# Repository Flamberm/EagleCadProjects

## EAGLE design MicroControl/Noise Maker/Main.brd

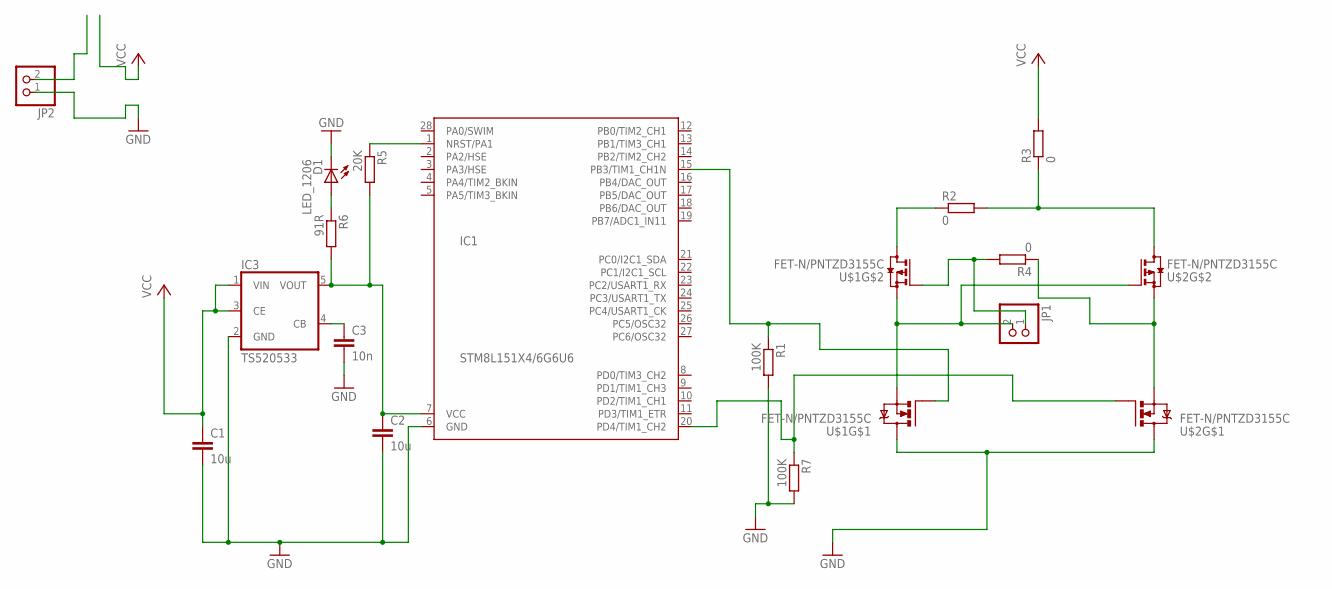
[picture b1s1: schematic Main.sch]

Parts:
C1, C2: 10u; C0805
C3: 10n; C0805
D1: LED_1206; LED1206
IC1: STM8L151X4/6G6U6; QFN28
IC3: TS520533; SOT25
JP1, JP2: PINHD-1X2; 1X02
R1, R7: 100K; R0805
R2, R3, R4: 0; R0805
R5: 20K; R0805
R6: 91R; R0805
U$1, U$2: FET-N/PNTZD3155C; SOT-563

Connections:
GND: C1.2, C2.2, C3.2, D1.C, IC1.6 (GND), IC3.2 (GND), JP2.1, R1.2, R7.2, U$1.6 (D), U$2.6 (D)
unnamed: D1.A, R6.1
unnamed: C3.1, IC3.4 (CB)
unnamed: IC1.1 (NRST/PA1), R5.1
unnamed: C2.1, IC1.7 (VCC), IC3.5 (VOUT), R5.2, R6.2
unnamed: R4.1, U$2.1 (S), U$2.4 (S)
unnamed: JP1.2, U$1.1 (S), U$1.4 (S), U$2.5 (G)
unnamed: IC1.20 (PD4/TIM1_CH2), R7.1, U$2.2 (G)
unnamed: R2.1, U$1.3 (D)
unnamed: R2.2, R3.1, U$2.3 (D)
unnamed: JP1.1, R4.2, U$1.5 (G)
unnamed: IC1.15 (PB3/TIM1_CH1N), R1.1, U$1.2 (G)
VCC: C1.1, IC3.1 (VIN), IC3.3 (CE), R3.2

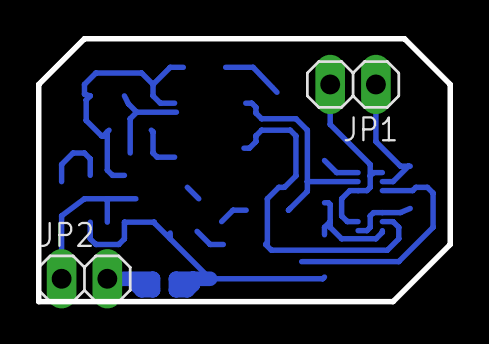
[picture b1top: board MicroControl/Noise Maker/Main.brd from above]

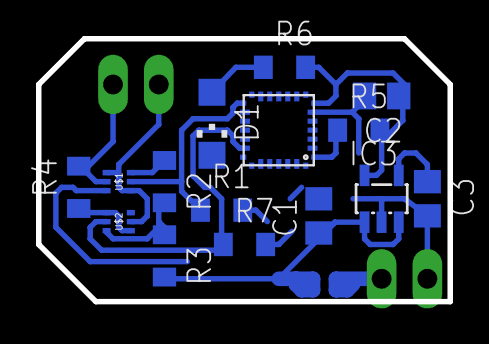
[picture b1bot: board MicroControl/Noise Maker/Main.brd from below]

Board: 2 copper layers, 22.9 x 14.6 mm, 17 parts (15 on the bottom side), 13 nets.

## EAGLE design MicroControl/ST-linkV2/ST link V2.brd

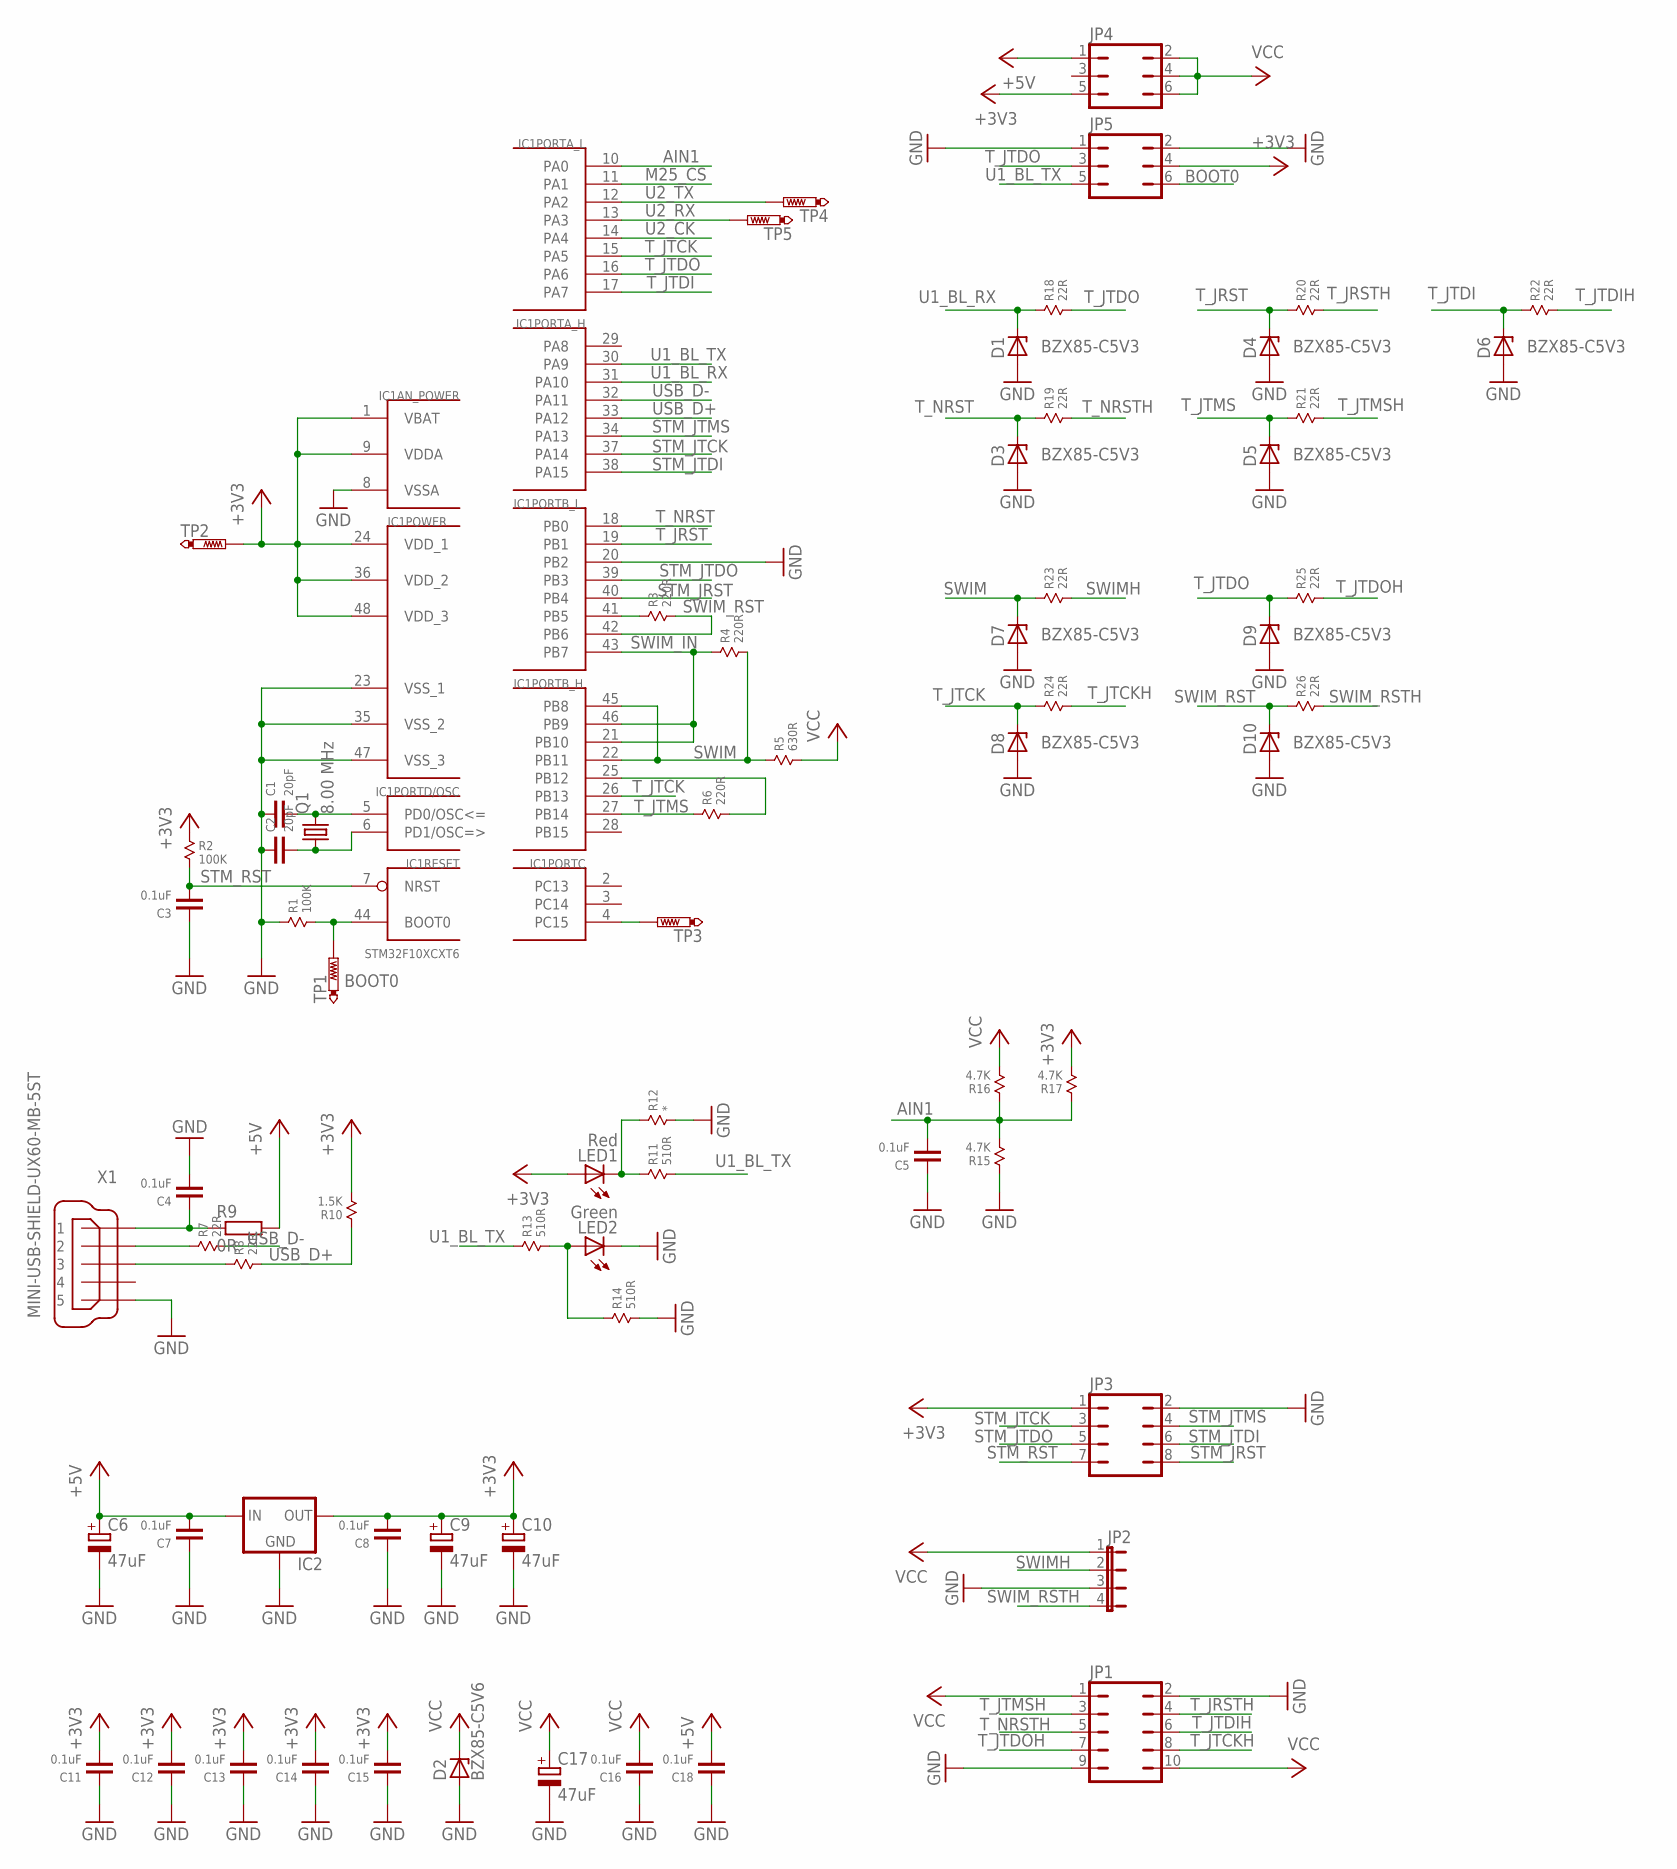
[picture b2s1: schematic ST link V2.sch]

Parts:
C1, C2: 20pF; X893_0805
C3, C4, C5, C7, C8, C11, C12, C13, C14, C15, C16, C18: 0.1uF; X893_0805
C6, C9, C10, C17: 47uF; SMC_B
D1, D3, D4, D5, D6, D7, D8, D9, D10: BZX85-C5V3; SOD80C
D2: BZX85-C5V6; SOD80C
IC1: STM32F10XCXT6; TQFP48
IC2: LM1117; SOT223
JP1: JP5Q
JP2: JP4E; JP4
JP3: JP4Q
JP4, JP5: JP3Q
LED1: Red; SML0805
LED2: Green; SML0805
Q1: 8.00 MHz; HC49U70
R1, R2: 100K; X893_0805
R3, R4, R6: 220R; X893_0805
R5: 630R; X893_0805
R7, R8, R18, R19, R20, R21, R22, R23, R24, R25, R26: 22R; X893_0805
R9: 0R; R1206
R10: 1.5K; X893_0805
R11, R13, R14: 510R; X893_0805
R12: *; X893_0805
R15, R16, R17: 4.7K; X893_0805
TP1, TP2, TP3, TP4, TP5: PTR1TP19R; TP19R
X1: MINI-USB-SHIELD-UX60-MB-5ST; UX60-MB-5ST

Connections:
+3V3: C8.1, C9.+, C10.+, C11.1, C12.1, C13.1, C14.1, C15.1, IC1.1 (VBAT), IC1.9 (VDDA), IC1.24 (VDD_1), IC1.36 (VDD_2), IC1.48 (VDD_3), IC2.2 (OUT), JP3.1, JP4.5, JP5.4, LED1.A, R2.1, R10.2, R17.2, TP2.TP
+5V: C6.+, C7.1, C18.1, IC2.3 (IN), JP4.1, R9.2
AIN1: C5.1, IC1.10 (PA0), R15.2, R16.1, R17.1
BOOT0: IC1.44 (BOOT0), JP5.6, R1.2, TP1.TP
GND: C1.2, C2.2, C3.2, C4.1, C5.2, C6.-, C7.2, C8.2, C9.-, C10.-, C11.2, C12.2, C13.2, C14.2, C15.2, C16.2, C17.-, C18.2, D1.A, D2.A, D3.A, D4.A, D5.A, D6.A, D7.A, D8.A, D9.A, D10.A, IC1.8 (VSSA), IC1.20 (PB2), IC1.23 (VSS_1), IC1.35 (VSS_2), IC1.47 (VSS_3), IC2.1 (GND), JP1.2, JP1.9, JP2.3, JP3.2, JP5.1, JP5.2, LED2.C, R1.1, R12.2, R14.2, R15.1, X1.5
M25_CS: IC1.11 (PA1)
unnamed: C1.1, IC1.5 (PD0/OSC<=), Q1.2
unnamed: C2.1, IC1.6 (PD1/OSC=>), Q1.1
unnamed: IC1.4 (PC15), TP3.TP
unnamed: C4.2, R9.1, X1.1
unnamed: IC1.25 (PB12), R6.2
unnamed: R7.1, X1.2
unnamed: R8.1, X1.3
unnamed: LED1.C, R11.1, R12.1
unnamed: IC1.41 (PB5), R3.1
unnamed: LED2.A, R13.2, R14.1
STM_JRST: IC1.40 (PB4), JP3.8
STM_JTCK: IC1.37 (PA14), JP3.3
STM_JTDI: IC1.38 (PA15), JP3.6
STM_JTDO: IC1.39 (PB3), JP3.5
STM_JTMS: IC1.34 (PA13), JP3.4
STM_RST: C3.1, IC1.7 (NRST), JP3.7, R2.2
SWIM: D7.C, IC1.22 (PB11), IC1.45 (PB8), R4.2, R5.1, R23.1
SWIMH: JP2.2, R23.2
SWIM_IN: IC1.21 (PB10), IC1.43 (PB7), IC1.46 (PB9), R4.1
SWIM_RST: D10.C, IC1.42 (PB6), R3.2, R26.1
SWIM_RSTH: JP2.4, R26.2
T_JRST: D4.C, IC1.19 (PB1), R20.1
T_JRSTH: JP1.4, R20.2
T_JTCK: D8.C, IC1.15 (PA5), IC1.26 (PB13), R24.1
T_JTCKH: JP1.8, R24.2
T_JTDI: D6.C, IC1.17 (PA7), R22.1
T_JTDIH: JP1.6, R22.2
T_JTDO: D9.C, IC1.16 (PA6), JP5.3, R18.2, R25.1
T_JTDOH: JP1.7, R25.2
T_JTMS: D5.C, IC1.27 (PB14), R6.1, R21.1
T_JTMSH: JP1.3, R21.2
T_NRST: D3.C, IC1.18 (PB0), R19.1
T_NRSTH: JP1.5, R19.2
U1_BL_RX: D1.C, IC1.31 (PA10), R18.1
U1_BL_TX: IC1.30 (PA9), JP5.5, R11.2, R13.1
U2_CK: IC1.14 (PA4)
U2_RX: IC1.13 (PA3), TP5.TP
U2_TX: IC1.12 (PA2), TP4.TP
USB_D+: IC1.33 (PA12), R8.2, R10.1
USB_D-: IC1.32 (PA11), R7.2
VCC: C16.1, C17.+, D2.C, JP1.1, JP1.10, JP2.1, JP4.2, JP4.4, JP4.6, R5.2, R16.2

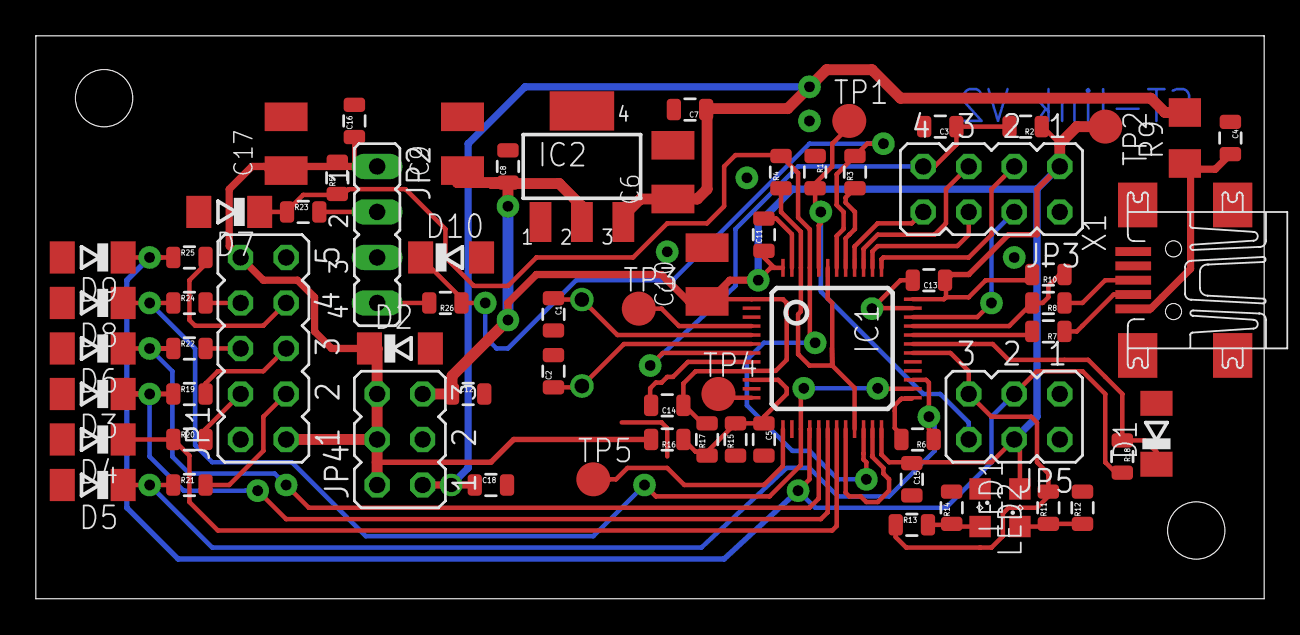
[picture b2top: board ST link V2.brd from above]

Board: 2 copper layers, 68.6 x 31.4 mm, 70 parts (1 on the bottom side), 45 nets.

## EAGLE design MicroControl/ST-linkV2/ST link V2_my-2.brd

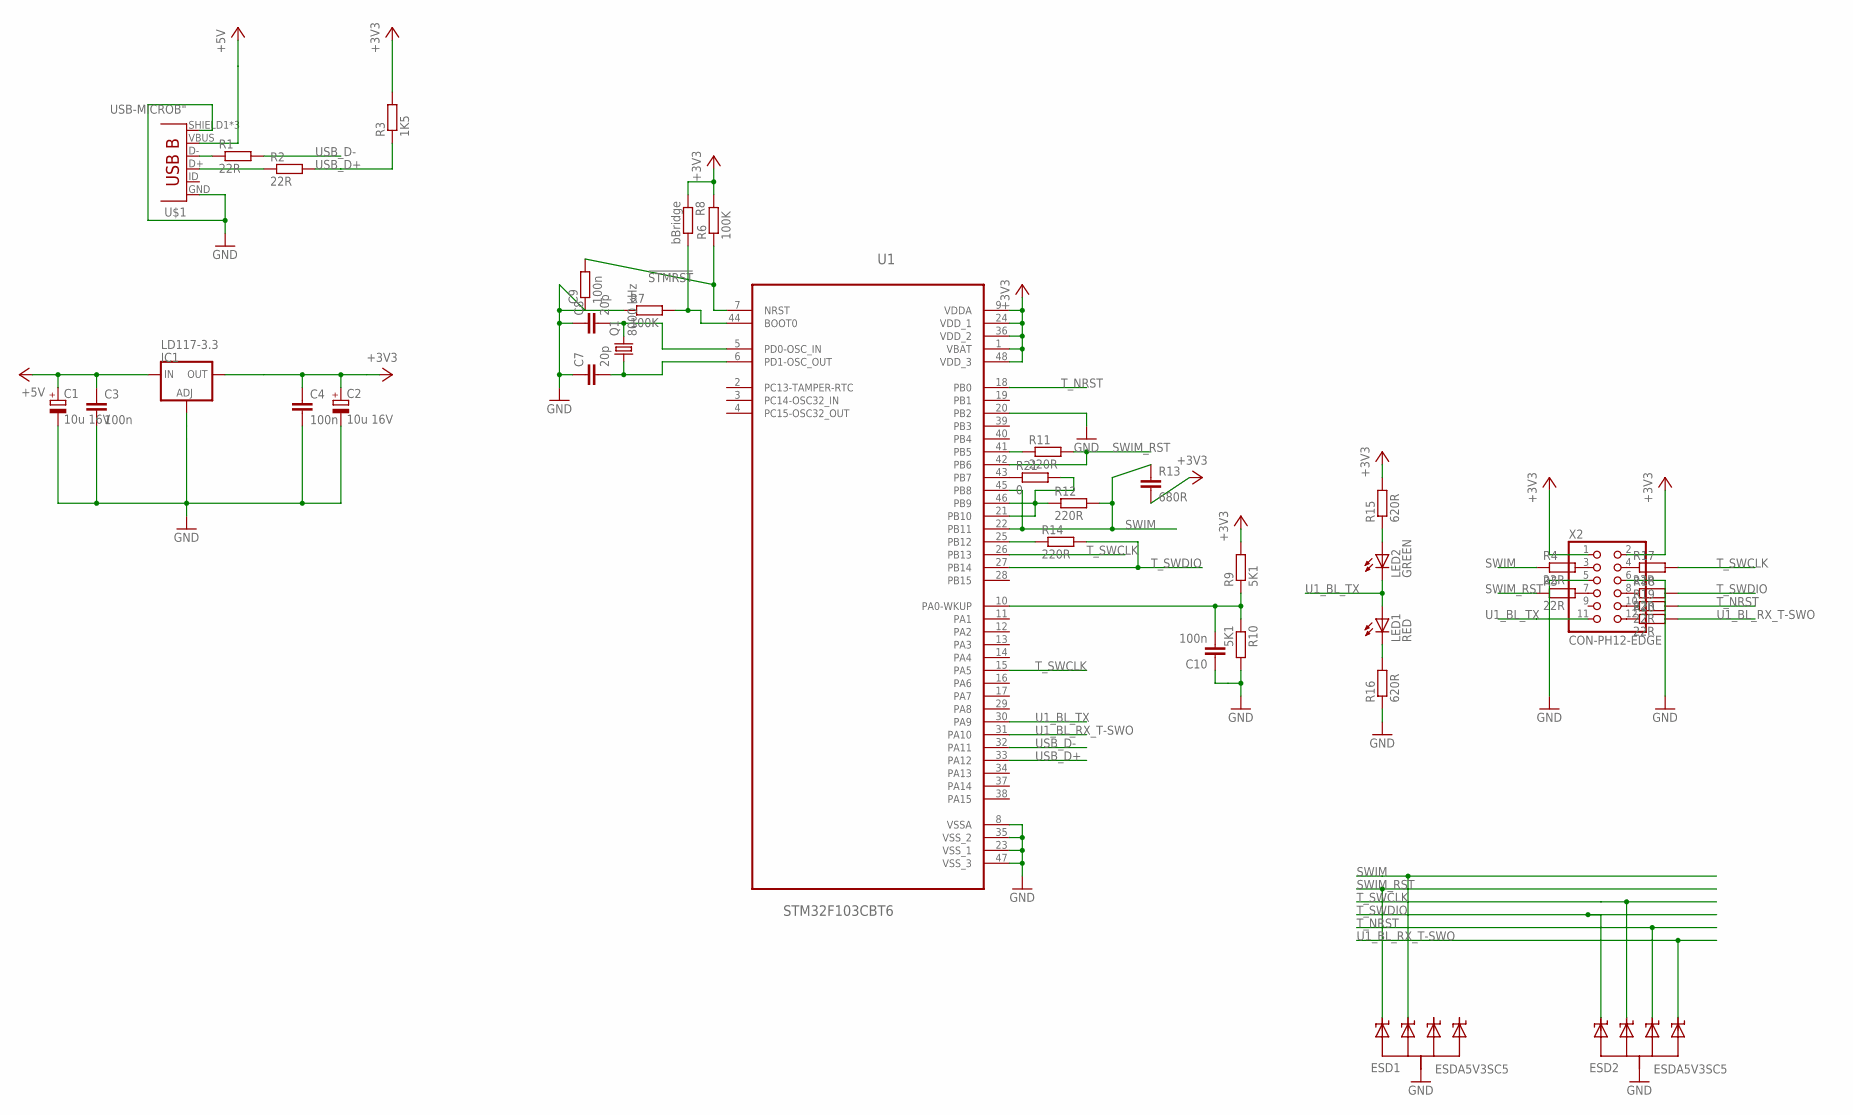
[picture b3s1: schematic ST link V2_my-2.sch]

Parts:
C1, C2: 10u 16V; SMC_A
C3, C4, C10: 100n; C0805
C7, C8: 20p; C0805
C9: 100n; R0805
ESD1, ESD2: ESDA5V3SC5; SOT23-5L
IC1: LD117-3.3; SOT223
LED1: RED; CHIPLED_1206
LED2: GREEN; CHIPLED_1206
Q1: 8000 kHz; HC49UP
R1, R2, R4, R5, R17, R18, R19, R20: 22R; R0805
R3: 1K5; R0805
R6, R7: 100K; R0805
R8: bBridge; R0805
R9, R10: 5K1; R0603
R11, R12, R14: 220R; R0805
R13: 680R; C0805
R15, R16: 620R; R0805
R21: 0; R0805
U1: STM32F103CBT6; QFP50P900X900X160-48N
U$1: USB-MICROB"; USB-B-MICRO-SMD_V03
X2: CON-PH12-EDGE; ML12_EDGE_SMD

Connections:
!STMRST: C9.2, R6.1, U1.7 (NRST)
+3V3: C2.+, C4.1, IC1.4 (OUT), R3.2, R6.2, R8.1, R9.2, R13.2, R15.2, U1.1 (VBAT), U1.9 (VDDA), U1.24 (VDD_1), U1.36 (VDD_2), U1.48 (VDD_3), X2.1, X2.2
+5V: C1.+, C3.1, IC1.3 (IN), U$1.VBUS
BOOT0: R7.2, R8.2, U1.44 (BOOT0)
GND: C1.-, C2.-, C3.2, C4.2, C7.1, C8.1, C9.1, C10.1, ESD1.2 (A), ESD2.2 (A), IC1.1 (ADJ), R7.1, R10.2, R16.1, U1.8 (VSSA), U1.20 (PB2), U1.23 (VSS_1), U1.35 (VSS_2), U1.47 (VSS_3), U$1.GND, U$1.SHIELD1 (SHIELD), U$1.SHIELD2 (SHIELD), U$1.SHIELD3 (SHIELD), X2.5, X2.6
unnamed: R1.1, U$1.D-
unnamed: R2.1, U$1.D+
unnamed: R4.2, X2.3
unnamed: C10.2, R9.1, R10.1, U1.10 (PA0-WKUP)
unnamed: R12.1, R21.2, U1.21 (PB10), U1.46 (PB9)
unnamed: C8.2, Q1.2, U1.5 (PD0-OSC_IN)
unnamed: C7.2, Q1.1, U1.6 (PD1-OSC_OUT)
unnamed: R11.1, U1.41 (PB5)
unnamed: R14.1, U1.25 (PB12)
unnamed: LED2.A, R15.1
unnamed: R5.2, X2.7
unnamed: LED1.C, R16.2
unnamed: R17.1, X2.4
unnamed: R18.1, X2.8
unnamed: R19.1, X2.10
unnamed: R20.1, X2.12
unnamed: R21.1, U1.43 (PB7)
SWIM: ESD1.3 (C2), R4.1, R12.2, R13.1, U1.22 (PB11), U1.45 (PB8)
SWIM_RST: ESD1.1 (C1), R5.1, R11.2, U1.42 (PB6)
T_NRST: ESD2.4 (C3), R19.2, U1.18 (PB0)
T_SWCLK: ESD2.3 (C2), R17.2, U1.15 (PA5), U1.26 (PB13)
T_SWDIO: ESD2.1 (C1), R14.2, R18.2, U1.27 (PB14)
U1_BL_RX_T-SWO: ESD2.5 (C4), R20.2, U1.31 (PA10)
U1_BL_TX: LED1.A, LED2.C, U1.30 (PA9), X2.11
USB_D+: R2.2, R3.1, U1.33 (PA12)
USB_D-: R1.2, U1.32 (PA11)

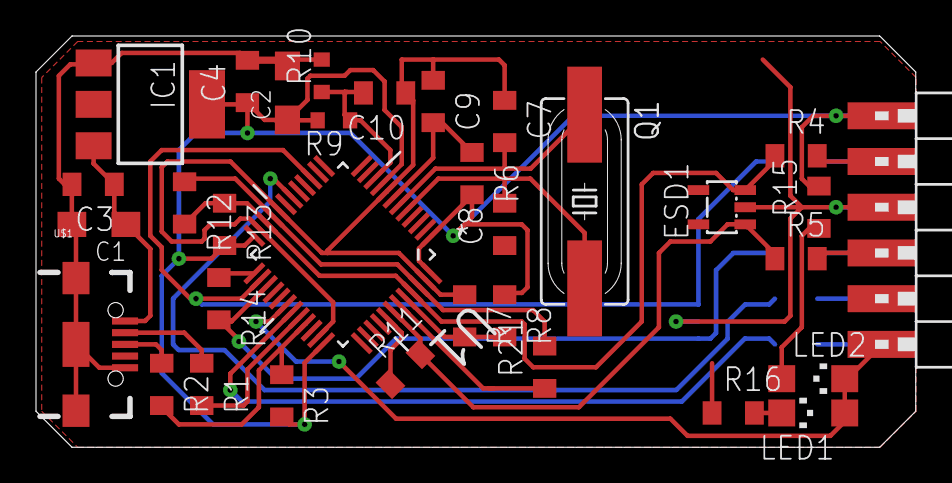
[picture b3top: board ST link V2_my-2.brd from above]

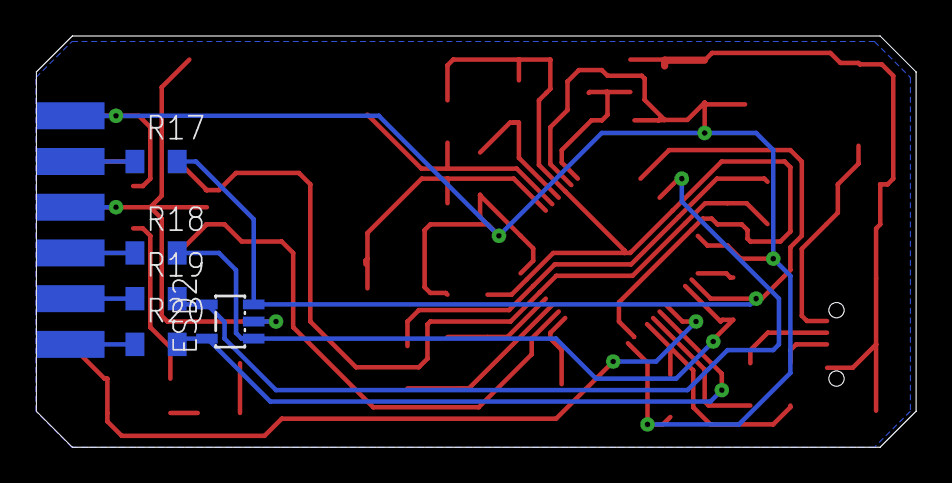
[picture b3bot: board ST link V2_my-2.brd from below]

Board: 2 copper layers, 48.9 x 22.8 mm, 38 parts (5 on the bottom side), 31 nets.

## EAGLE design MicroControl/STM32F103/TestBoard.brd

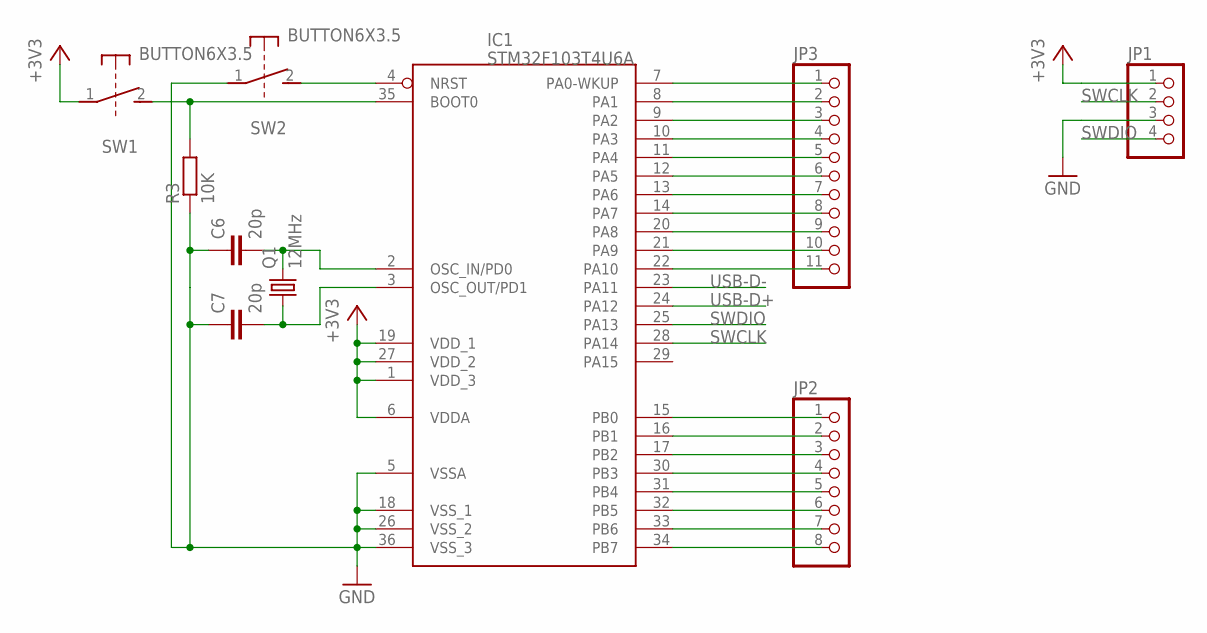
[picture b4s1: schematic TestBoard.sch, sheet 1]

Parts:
C6, C7: 20p; CAP0805
IC1: STM32F103T4U6A; QFN50P606X606X100-36
JP1: PINHD-1X4; 1X04
JP2: PINHD-1X8; 1X08
JP3: PINHD-1X11; 1X11
Q1: 12MHz; HC49UP
R3: 10K; RESC2012X50
SW1, SW2: BUTTON6X3.5; SW-6X3.5

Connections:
+3V3: IC1.1 (VDD_3), IC1.6 (VDDA), IC1.19 (VDD_1), IC1.27 (VDD_2), JP1.1, SW1.1; also elsewhere on the board
GND: C6.1, C7.1, IC1.5 (VSSA), IC1.18 (VSS_1), IC1.26 (VSS_2), IC1.36 (VSS_3), JP1.3, R3.1, SW2.1; also elsewhere on the board
unnamed: C7.2, IC1.3 (OSC_OUT/PD1), Q1.1
unnamed: C6.2, IC1.2 (OSC_IN/PD0), Q1.2
unnamed: IC1.35 (BOOT0), R3.2, SW1.2
unnamed: IC1.4 (NRST), SW2.2
unnamed: IC1.15 (PB0), JP2.1
unnamed: IC1.16 (PB1), JP2.2
unnamed: IC1.17 (PB2), JP2.3
unnamed: IC1.30 (PB3), JP2.4
unnamed: IC1.31 (PB4), JP2.5
unnamed: IC1.32 (PB5), JP2.6
unnamed: IC1.33 (PB6), JP2.7
unnamed: IC1.34 (PB7), JP2.8
unnamed: IC1.7 (PA0-WKUP), JP3.1
unnamed: IC1.8 (PA1), JP3.2
unnamed: IC1.9 (PA2), JP3.3
unnamed: IC1.10 (PA3), JP3.4
unnamed: IC1.11 (PA4), JP3.5
unnamed: IC1.12 (PA5), JP3.6
unnamed: IC1.13 (PA6), JP3.7
unnamed: IC1.14 (PA7), JP3.8
unnamed: IC1.20 (PA8), JP3.9
unnamed: IC1.21 (PA9), JP3.10
unnamed: IC1.22 (PA10), JP3.11
SWCLK: IC1.28 (PA14), JP1.2
SWDIO: IC1.25 (PA13), JP1.4
USB-D+: IC1.24 (PA12); also elsewhere on the board
USB-D-: IC1.23 (PA11); also elsewhere on the board

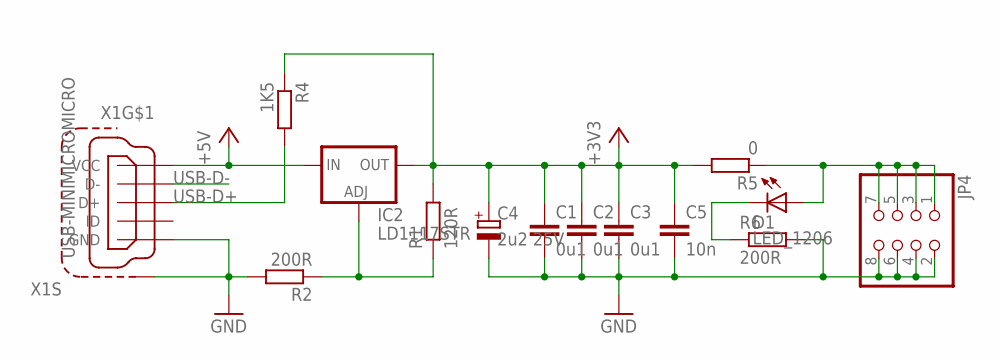
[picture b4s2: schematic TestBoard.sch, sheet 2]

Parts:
C1, C2, C3: 0u1; CAP0805
C4: 2u2 25V; CAPMP3317X180
C5: 10n; CAP0805
D1: LED_1206; LED1206
IC2: LD1117STR; SOT230P700X180-4
JP4: PINHD-2X4; 2X04
R1: 120R; RESC2012X50
R2, R6: 200R; RESC2012X50
R4: 1K5; RESC2012X50
R5: 0; RESC2012X50
X1: USB-MINIMICROMICRO; USB-B-MICRO-SMD

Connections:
+3V3: C1.1, C2.1, C3.1, C4.1 (+), C5.1, IC2.2 (OUT), IC2.4 (OUT), R1.2, R4.1, R5.2; also elsewhere on the board
+5V: IC2.3 (IN), X1.VBUS (VCC)
GND: C1.2, C2.2, C3.2, C4.2 (-), C5.2, JP4.2, JP4.4, JP4.6, JP4.8, R2.2, R6.2, X1.GND, X1.SHIELD1 (S1), X1.SHIELD2 (S1), X1.SHIELD3 (S1); also elsewhere on the board
unnamed: IC2.1 (ADJ), R1.1, R2.1
unnamed: D1.A, JP4.1, JP4.3, JP4.5, JP4.7, R5.1
unnamed: D1.C, R6.1
USB-D+: R4.2, X1.D+; also elsewhere on the board
USB-D-: X1.D-; also elsewhere on the board

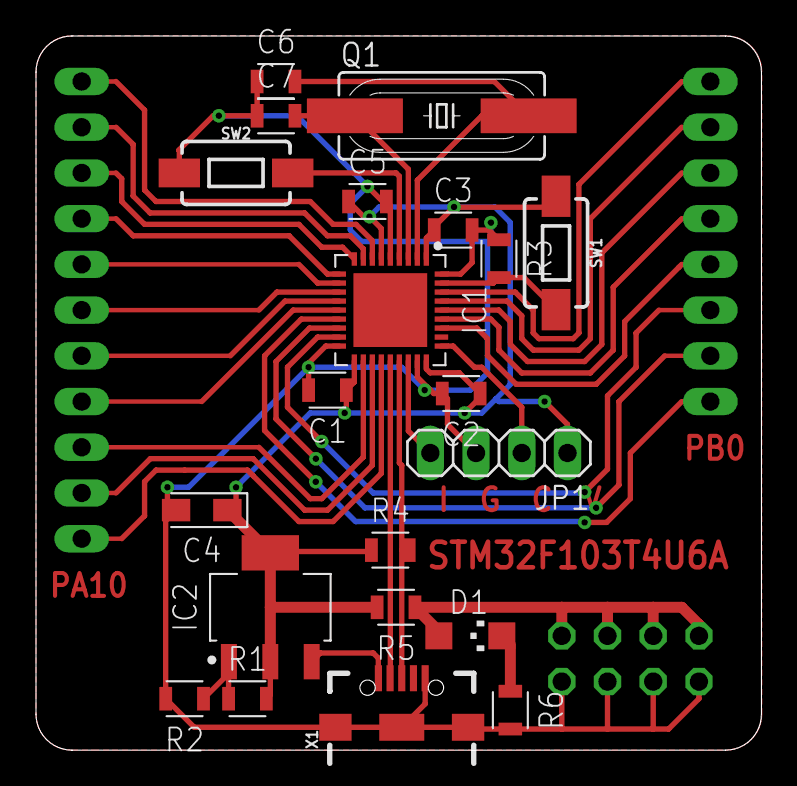
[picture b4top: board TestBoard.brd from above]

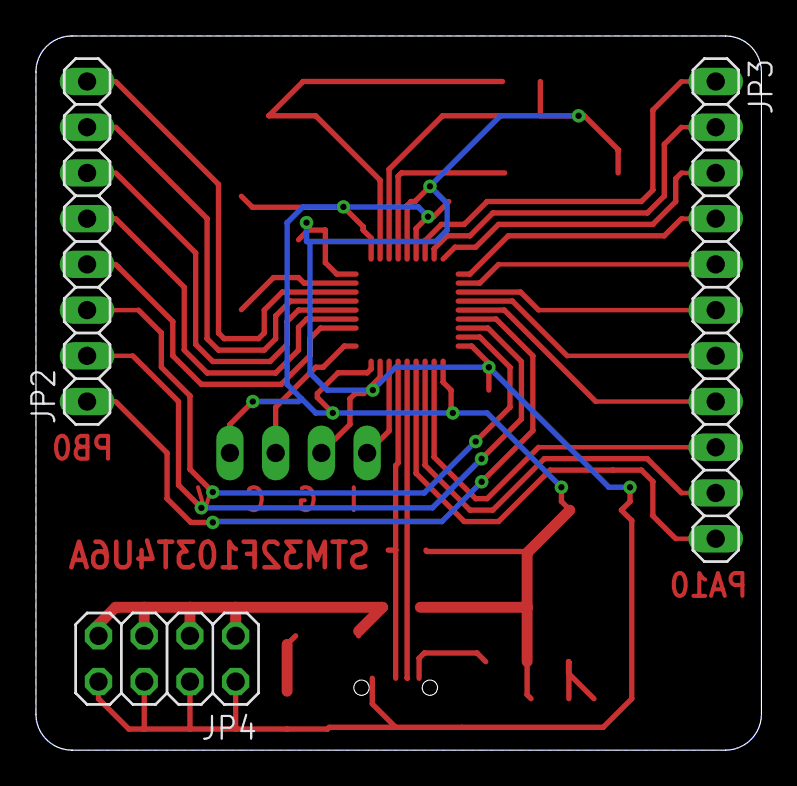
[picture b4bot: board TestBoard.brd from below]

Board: 2 copper layers, 40.3 x 39.7 mm, 24 parts (3 on the bottom side), 33 nets.

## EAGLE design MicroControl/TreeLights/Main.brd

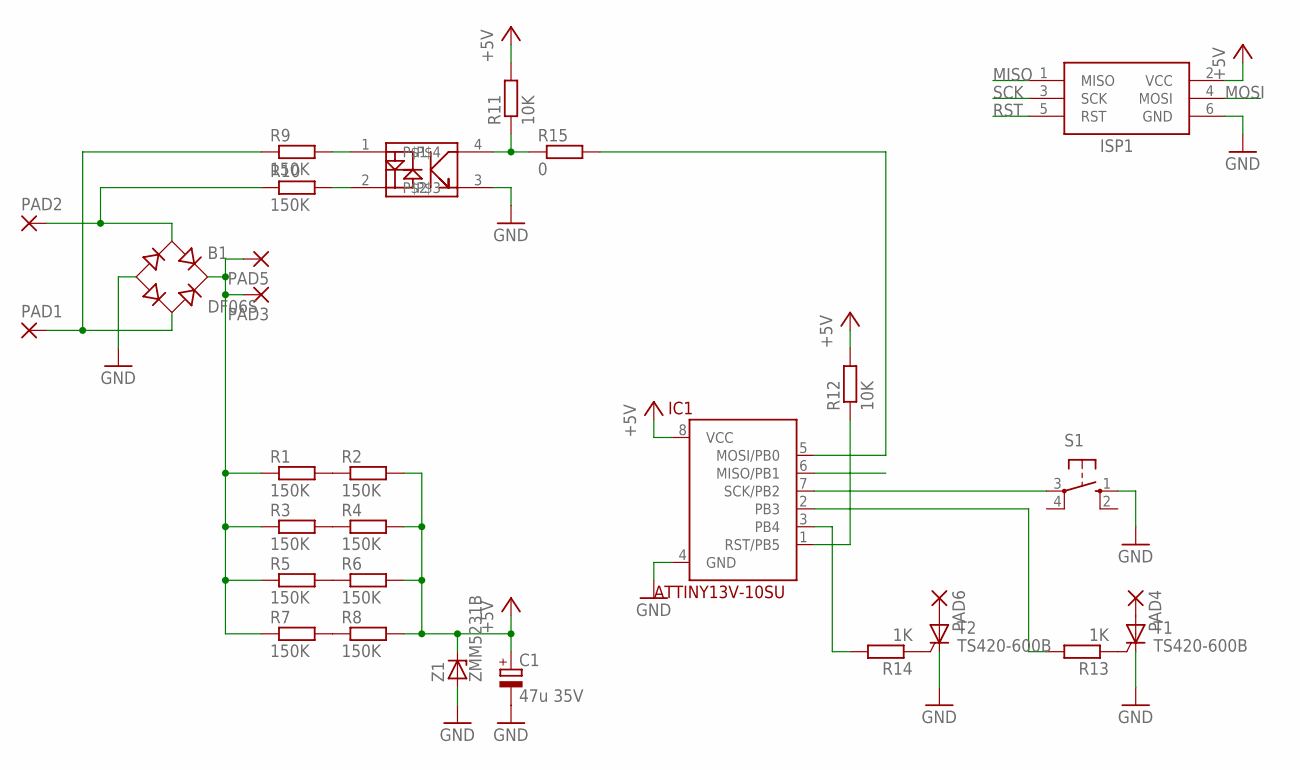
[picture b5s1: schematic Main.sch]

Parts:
B1: DF06S; DFS
C1: 47u 35V; CT7343
IC1: ATTINY13V-10SU; SOIC8
ISP1: AVRISP-6; AVRISP
PAD1, PAD2, PAD3, PAD4, PAD5, PAD6: SMD5; SMD2,54-5,08
R1, R2, R3, R4, R5, R6, R7, R8, R9, R10: 150K; R1206
R11, R12: 10K; R1206
R13, R14: 1K; R1206
R15: 0; R0805
S1: 10-XX; B3F-10XX
T1, T2: TS420-600B; DPAK
U$1: OPTO-EL3H4(TA)-VG; SSOP4
Z1: ZMM5231B; MINIMELF

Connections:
+5V: C1.+, IC1.8 (VCC), ISP1.2 (VCC), R2.2, R4.2, R6.2, R8.2, R11.2, R12.2, Z1.C
GND: B1.-, C1.-, IC1.4 (GND), ISP1.6 (GND), S1.1 (S), T1.G (C), T2.G (C), U$1.3, Z1.A
MISO: IC1.6 (MISO/PB1), ISP1.1 (MISO)
MOSI: IC1.5 (MOSI/PB0), ISP1.4 (MOSI), R15.2
unnamed: R10.2, U$1.2
unnamed: R9.2, U$1.1
unnamed: R1.2, R2.1
unnamed: R3.2, R4.1
unnamed: R5.2, R6.1
unnamed: R7.2, R8.1
unnamed: B1.+, PAD3.1, PAD5.1, R1.1, R3.1, R5.1, R7.1
unnamed: PAD4.1, T1.D (A)
unnamed: PAD6.1, T2.D (A)
unnamed: R13.1, T1.S (G)
unnamed: R14.1, T2.S (G)
unnamed: B1.AC2, PAD1.1, R9.1
unnamed: B1.AC1, PAD2.1, R10.1
unnamed: IC1.3 (PB4), R14.2
unnamed: IC1.2 (PB3), R13.2
unnamed: R11.1, R15.1, U$1.4
RST: IC1.1 (RST/PB5), ISP1.5 (RST), R12.1
SCK: IC1.7 (SCK/PB2), ISP1.3 (SCK), S1.3

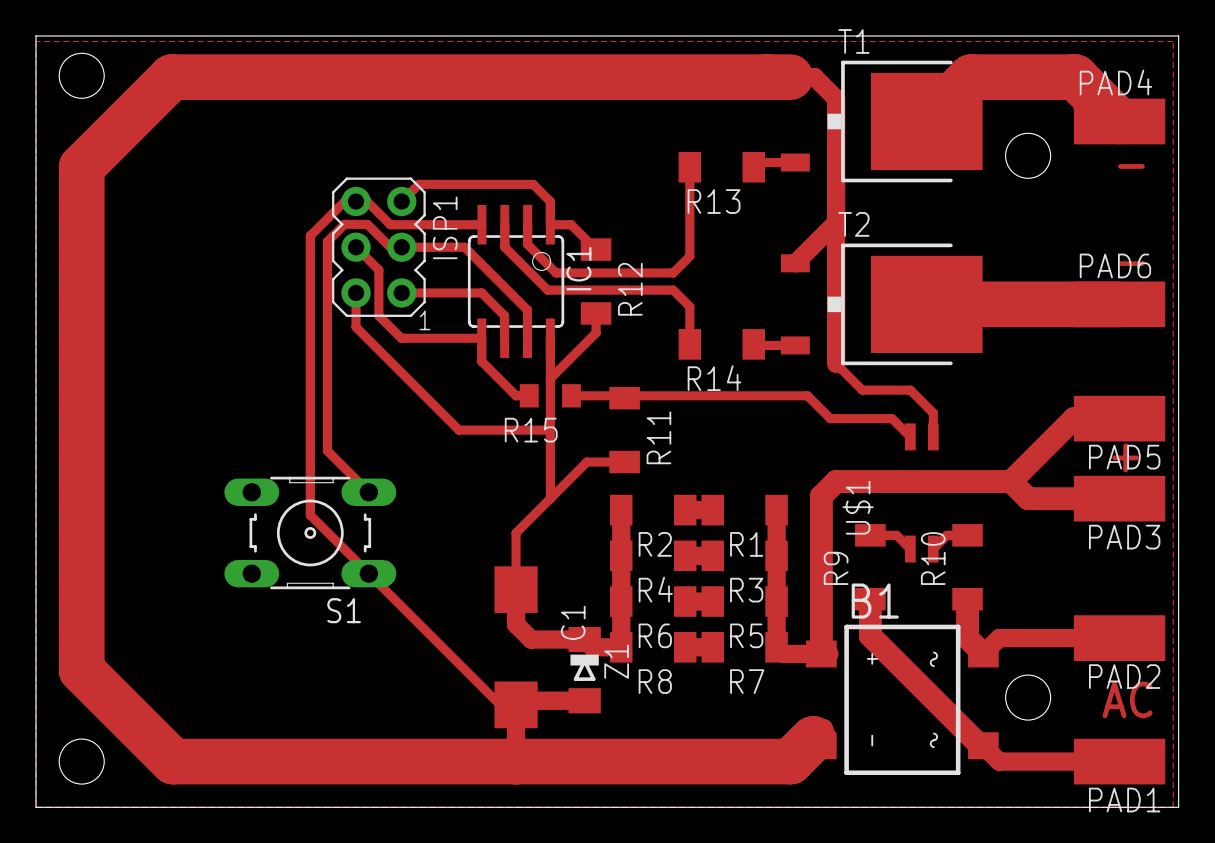
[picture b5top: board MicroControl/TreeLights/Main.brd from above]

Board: 2 copper layers, 63.5 x 42.9 mm, 30 parts (0 on the bottom side), 22 nets.

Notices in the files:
parts and their libraries:
SparkFun-Connectors: Licensing: Creative Commons ShareAlike 4.0 International - https://creativecommons.org/licenses/by-sa/4.0
